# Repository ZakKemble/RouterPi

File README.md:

# RouterPi

Another Raspberry Pi router!

https://blog.zakkemble.net/routerpi-compute-module-4-router/

--------

Zak Kemble

contact@zakkemble.net

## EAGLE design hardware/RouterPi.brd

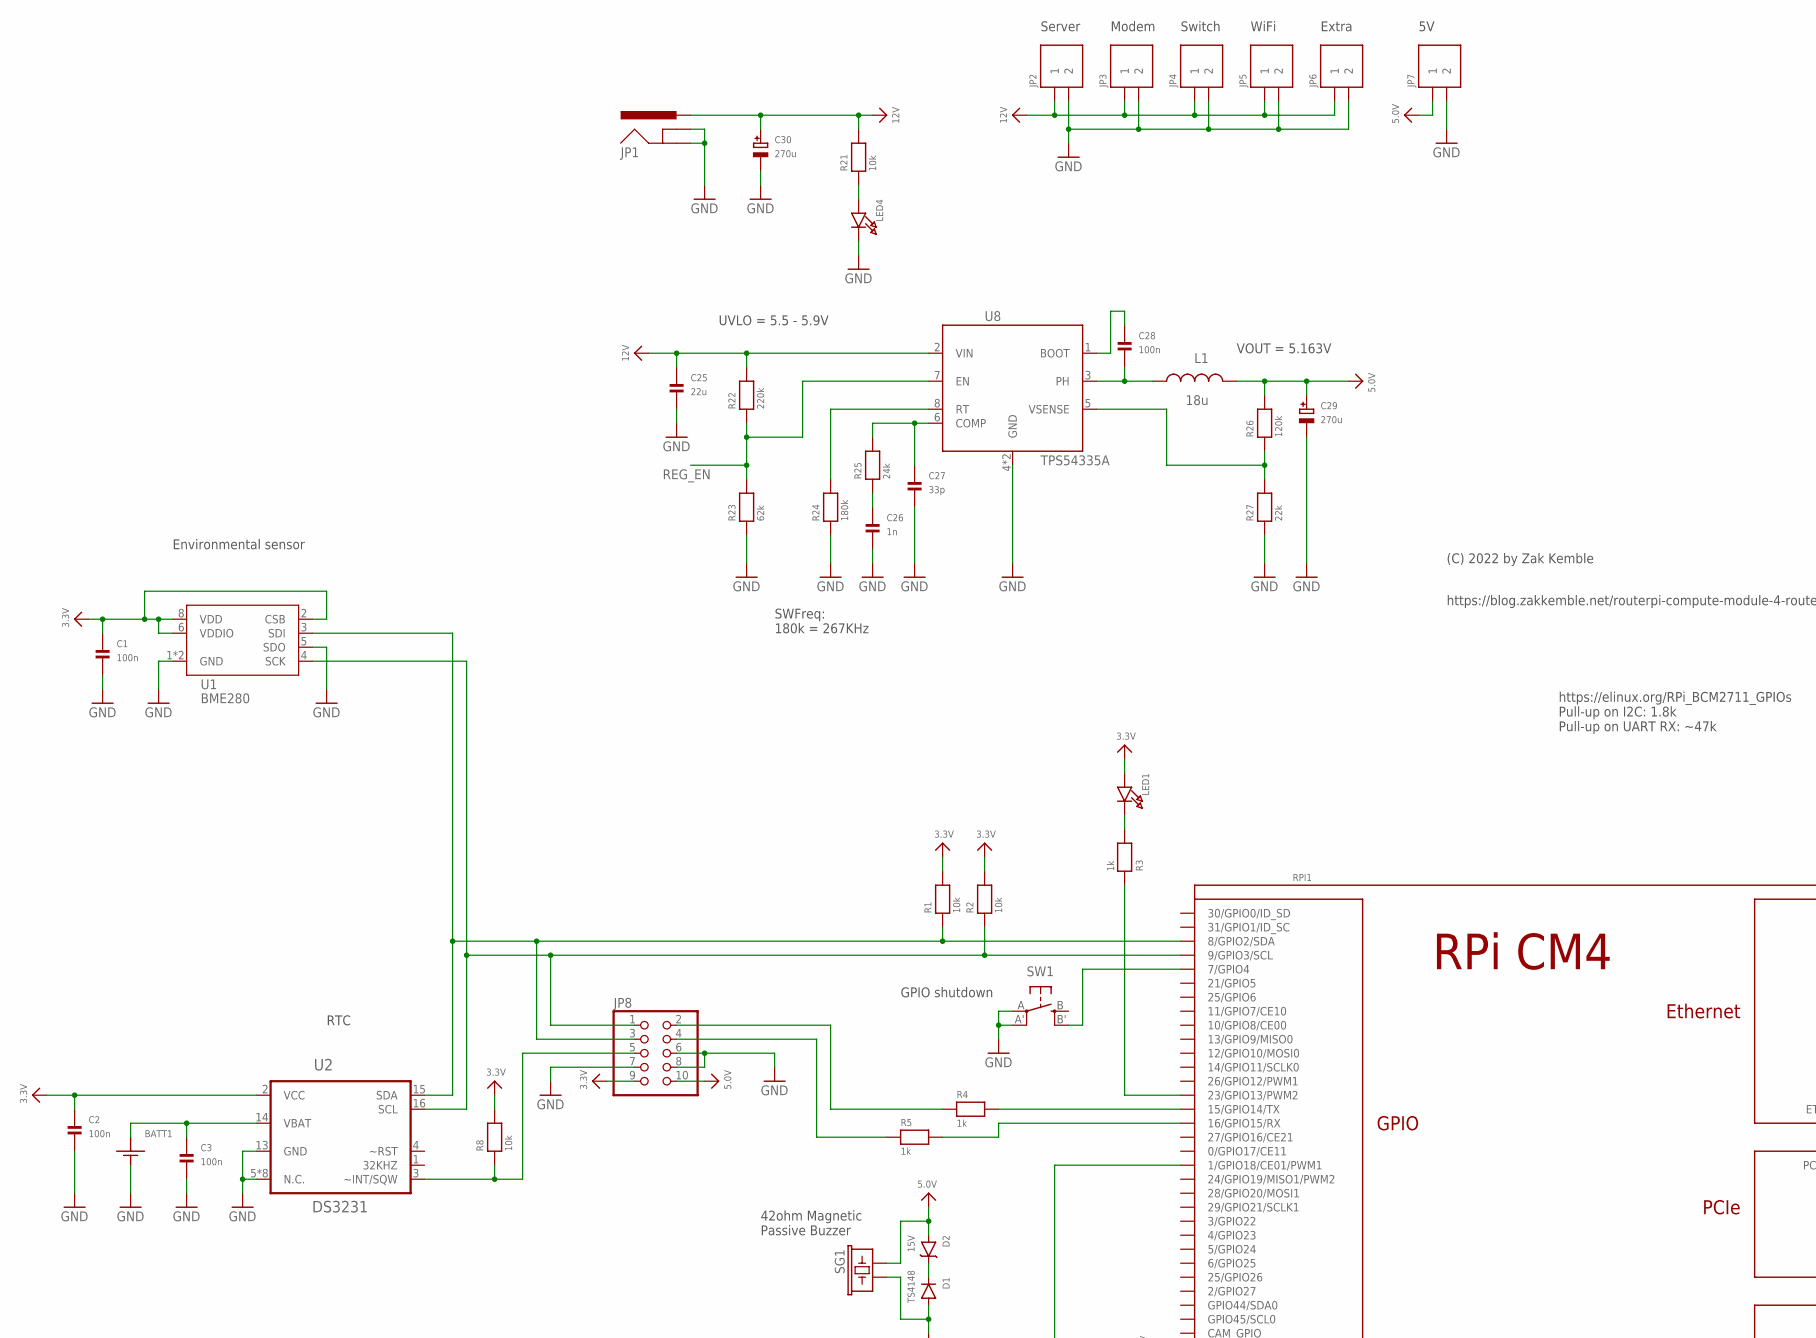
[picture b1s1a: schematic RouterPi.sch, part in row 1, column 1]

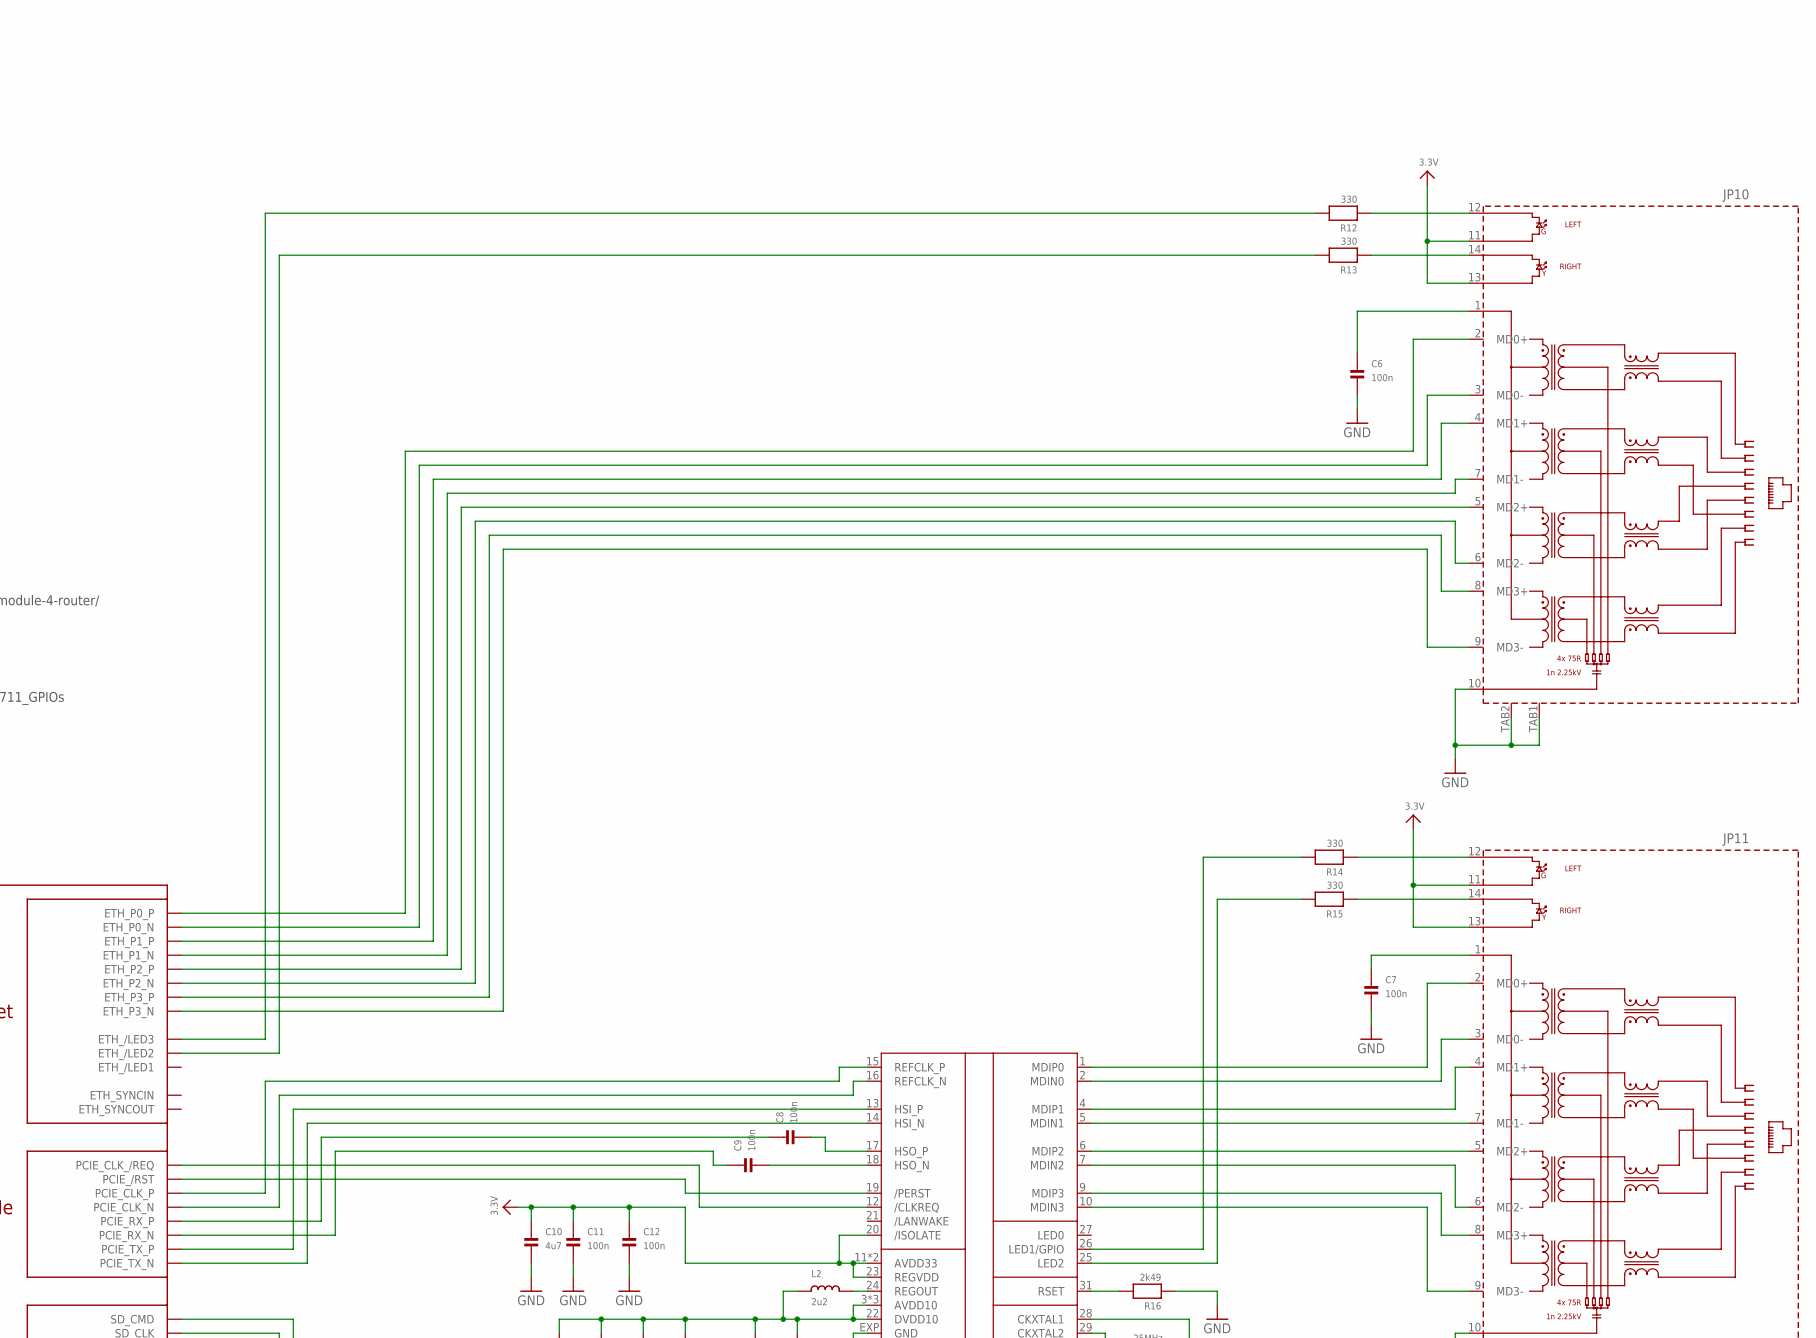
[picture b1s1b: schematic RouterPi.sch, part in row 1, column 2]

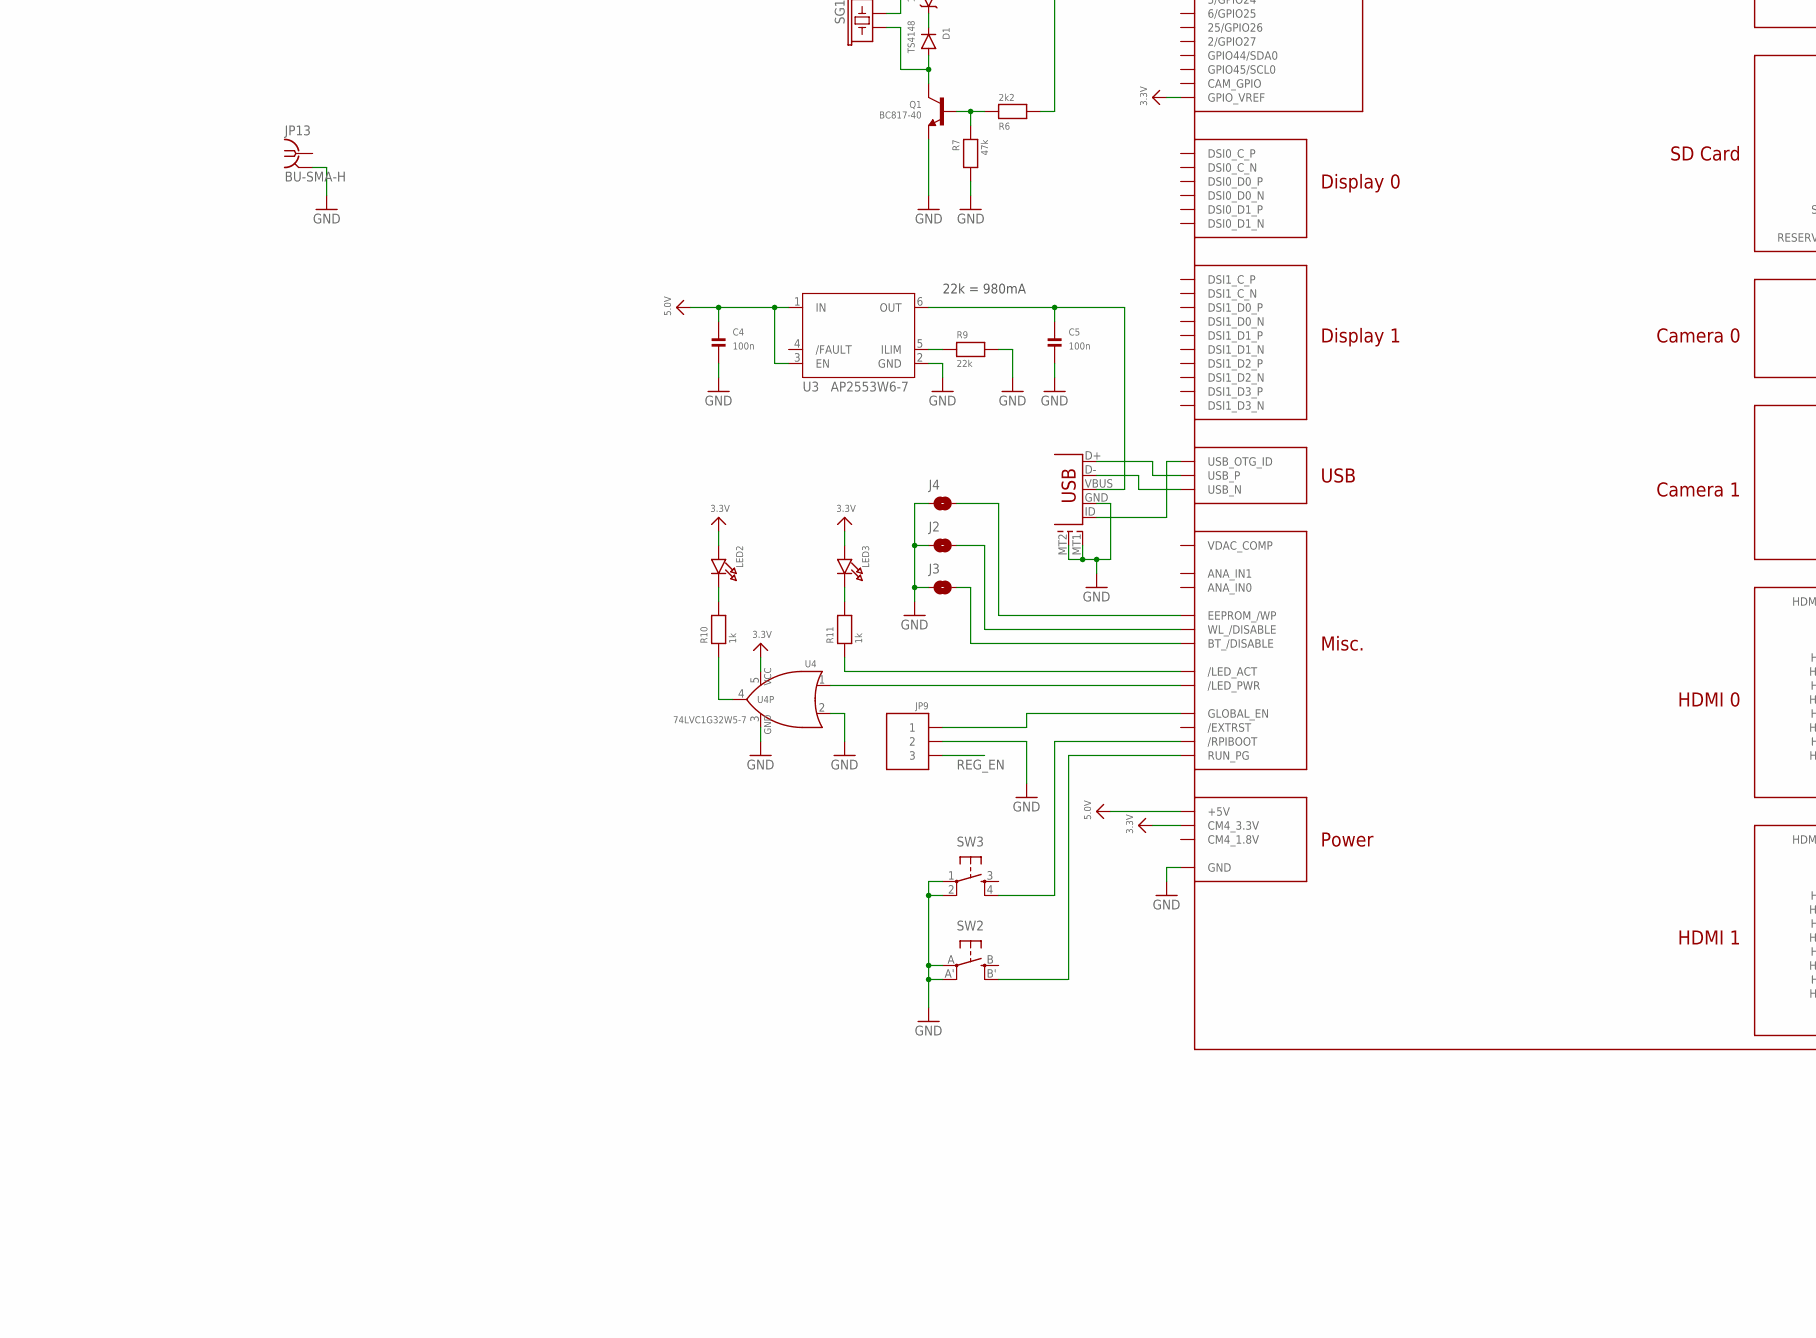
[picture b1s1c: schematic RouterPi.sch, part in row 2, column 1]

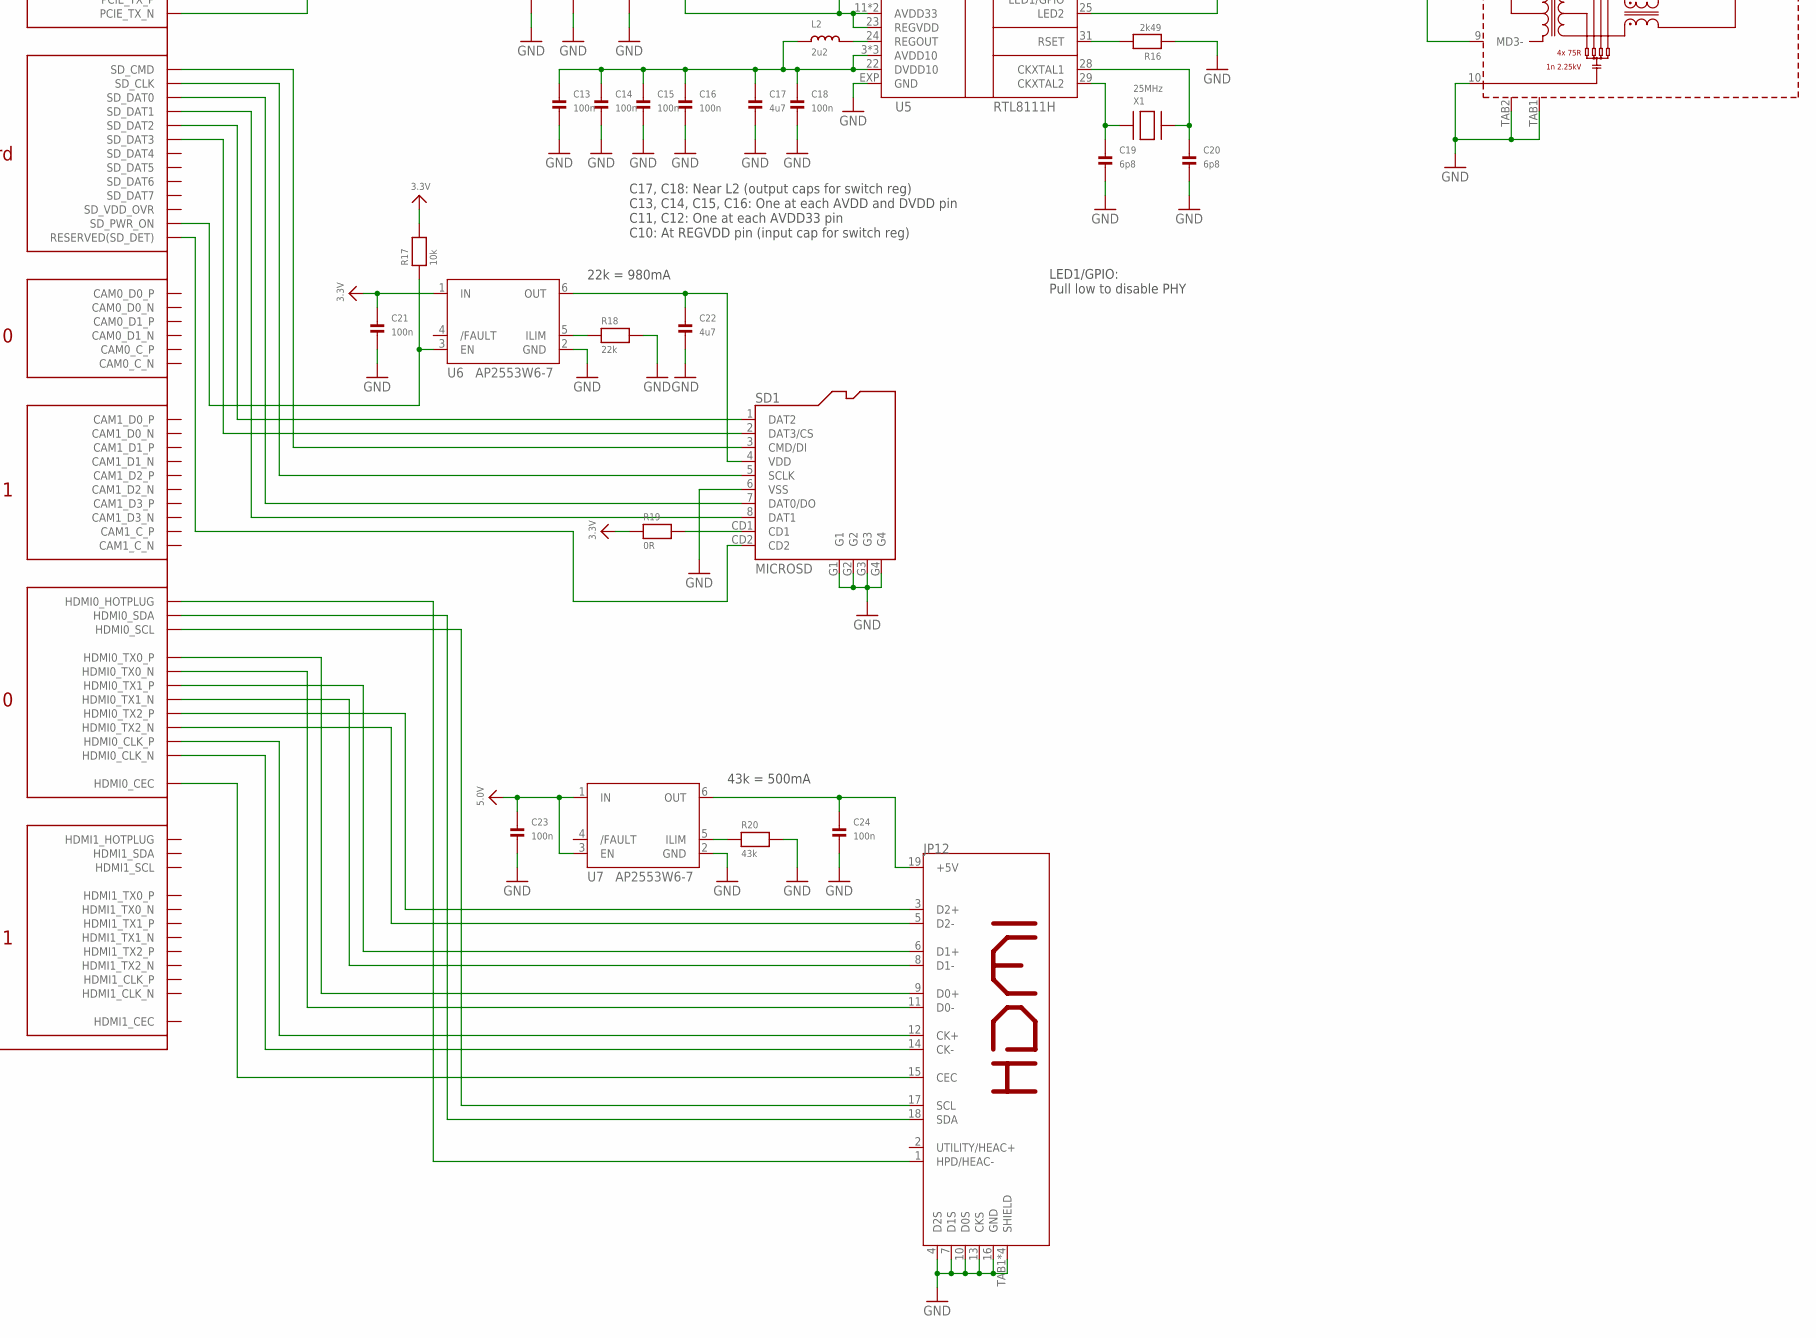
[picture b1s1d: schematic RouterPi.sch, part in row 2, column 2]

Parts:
BATT1: BATTERY_CR927
C1, C2, C3, C4, C5, C6, C7, C8, C9, C11, C12, C13, C14, C15, C16, C18, C21, C23, C24, C28: 100n; 0402_XSMALL
C10, C17: 4u7; _0603MP; FARNELL 2611924
C19, C20: 6p8; 0402_XSMALL
C22: 4u7; _0603MP
C25: 22u; 1210K; PARTNUM C3225X5R1C226M250AA; FARNELL 2526285
C26: 1n; 0402_XSMALL
C27: 33p; 0402_XSMALL
C29, C30: 270u; PANASONIC_D; PARTNUM 16SVPG270M; FARNELL 2491823
D1: TS4148; 0805_DIODE
D2: 15V; SOT-23-SLIMPAD; PARTNUM BZX84-C15
J2, J3, J4: JUMPERSMALL; JUMPER_SMALL
JP1: POWER_JACKPTH_HIGHCURRENT; POWER_JACK_PTH_HIGHCURRENT
JP2, JP3, JP4, JP5, JP6, JP7: 2WAY
JP8: PINHD-2X5; 2X05
JP9: HEADER_3WAY2.0MM; HEADER_2.0_3WAY
JP10, JP11: RJ45_MAG_MOLEX_93626
JP12: HDMIMICRO2; HDMI_MICRO2
JP13: BU-SMA-H
L1: 18u; CDRH125; PARTNUM SRR1210-180M; FARNELL 2408814
L2: 2u2; INDUCTOR_3X3MM_SM; FARNELL 2616857
LED1, LED2, LED3, LED4: LED0603_NOOUTLINE; CHIPLED_0603_NOOUTLINE
Q1: BC817-40; SOT23-R
R1, R2, R8, R17, R21: 10k; 0402_XSMALL
R3, R4, R5, R10, R11: 1k; 0402_XSMALL
R6: 2k2; 0402_XSMALL
R7: 47k; 0402_XSMALL
R9, R18, R27: 22k; 0402_XSMALL
R12, R13, R14, R15: 330; 0402_XSMALL
R16: 2k49; 0402_XSMALL
R19: 0R; 0402_XSMALL
R20: 43k; 0402_XSMALL
R22: 220k; 0402_XSMALL
R23: 62k; 0402_XSMALL
R24: 180k; 0402_XSMALL
R25: 24k; 0402_XSMALL
R26: 120k; 0402_XSMALL
RPI1: RPI_CM4RPI_CM4; RPI_CM4
SD1: MICROSD
SG1: BUZZERPTH; BUZZER-12MM
SW1, SW2: SPST_TACTMC32882; TACT_SMD4
SW3: SPST_TACTG75_3X4; TACT_SMD5
U1: BME280
U2: DS3231; SOIC127P1032X265-16N
U3, U6, U7: AP2553W6-7; SOT23-6_SM_PAD
U4: 74LVC1G32W5-7; SOT23-5_SM_PAD
U5: RTL8111H; QFN32-4X4-0.4
U8: TPS54335A; SOIC8_150MIL_EXPPAD
USB1: USB-MICROBLARGEPAD; USB-MICROB_LARGEPAD
X1: 25MHz; 2016_XTAL; PARTNO MCSJK-7F-25.00-10-20-60-B-20; FARNELL 2853847

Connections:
3.3V: C1.1, C2.1, C10.1, C11.1, C12.1, C21.1, JP8.9, JP10.11 (LED_L_A), JP10.13 (LED_R_A), JP11.11 (LED_L_A), JP11.13 (LED_R_A), LED1.A, LED2.A, LED3.A, R1.2, R2.2, R8.2, R17.2, R19.1, RPI1.78 (GPIO_VREF), RPI1.84 (CM4_3.3V), RPI1.86 (CM4_3.3V), U1.2 (CSB), U1.6 (VDDIO), U1.8 (VDD), U2.2 (VCC), U4.5 (VCC), U5.11 (AVDD33), U5.20 (/ISOLATE), U5.23 (REGVDD), U5.32 (AVDD33), U6.1 (IN)
5.0V: C4.1, C23.1, C29.+, D2.2 (A), JP7.P$1 (1), JP8.10, L1.2, R26.2, RPI1.77 (+5V), RPI1.79 (+5V), RPI1.81 (+5V), RPI1.83 (+5V), RPI1.85 (+5V), RPI1.87 (+5V), SG1.+ (1), U3.1 (IN), U3.3 (EN), U7.1 (IN), U7.3 (EN)
12V: C25.1, C30.+, JP1.PWR, JP2.P$1 (1), JP3.P$1 (1), JP4.P$1 (1), JP5.P$1 (1), JP6.P$1 (1), R21.2, R22.2, U8.2 (VIN)
GND: BATT1.B- (NEG), C1.2, C2.2, C3.2, C4.2, C5.2, C6.2, C7.2, C10.2, C11.2, C12.2, C13.2, C14.2, C15.2, C16.2, C17.2, C18.2, C19.2, C20.2, C21.2, C22.2, C23.2, C24.2, C25.2, C26.2, C27.2, C29.-, C30.-, J2.1, J3.1, J4.1, JP1.C1 (GNDBREAK), JP1.C2 (GNDBREAK), JP1.C3 (GNDBREAK), JP1.C4 (GNDBREAK), JP1.GND, JP2.P$2 (2), JP3.P$2 (2), JP4.P$2 (2), JP5.P$2 (2), JP6.P$2 (2), JP7.P$2 (2), JP8.6, JP8.7, JP8.8, JP9.2, JP10.10 (GND), JP10.TAB1, JP10.TAB2, JP11.10 (GND), JP11.TAB1, JP11.TAB2, JP12.4 (D2S), JP12.7 (D1S), JP12.10 (D0S), JP12.13 (CKS), JP12.16 (GND), JP12.TAB1 (SHIELD), JP12.TAB2 (SHIELD), JP12.TAB3 (SHIELD), JP12.TAB4 (SHIELD), JP13.2, JP13.3 (2), JP13.4 (2), JP13.5 (2), LED4.C, Q1.2 (E), R7.2, R9.2, R16.1, R18.2, R20.2, R23.1, R24.1, R27.1, RPI1.1 (GND), RPI1.2 (GND), RPI1.7 (GND), RPI1.8 (GND), RPI1.13 (GND), RPI1.14 (GND), RPI1.22 (GND), RPI1.23 (GND), RPI1.32 (GND), RPI1.33 (GND), RPI1.42 (GND), RPI1.43 (GND), RPI1.52 (GND), RPI1.53 (GND), RPI1.59 (GND), RPI1.60 (GND), RPI1.65 (GND), RPI1.66 (GND), RPI1.71 (GND), RPI1.74 (GND), RPI1.98 (GND), RPI1.107 (GND), RPI1.108 (GND), RPI1.113 (GND), RPI1.114 (GND), RPI1.119 (GND), RPI1.120 (GND), RPI1.125 (GND), RPI1.126 (GND), RPI1.131 (GND), RPI1.132 (GND), RPI1.137 (GND), RPI1.138 (GND), RPI1.144 (GND), RPI1.150 (GND), RPI1.155 (GND), RPI1.156 (GND), RPI1.161 (GND), RPI1.162 (GND), RPI1.167 (GND), RPI1.168 (GND), RPI1.173 (GND), RPI1.174 (GND), RPI1.179 (GND), RPI1.180 (GND), RPI1.185 (GND), RPI1.186 (GND), RPI1.191 (GND), RPI1.192 (GND), RPI1.197 (GND), RPI1.198 (GND), SD1.6 (VSS), SD1.G1, SD1.G2, SD1.G3, SD1.G4, SW1.A, SW1.A' (P1), SW2.A, SW2.A' (P1), SW3.1, SW3.2 (P1), U1.1 (GND), U1.5 (SDO), U1.7 (GND), U2.5 (N.C.), U2.6 (N.C.), U2.7 (N.C.), U2.8 (N.C.), U2.9 (N.C.), U2.10 (N.C.), U2.11 (N.C.), U2.12 (N.C.), U2.13 (GND), U3.2 (GND), U4.2 (B), U4.3 (GND), U5.EXP (GND), U6.2 (GND), U7.2 (GND), U8.4 (GND), U8.EXPPAD (GND), USB1.GND, USB1.MT1 (SHEILD1), USB1.MT2 (SHEILD2)
unnamed: C28.1, U8.1 (BOOT)
unnamed: R10.1, U4.4 (Y)
unnamed: R24.2, U8.8 (RT)
unnamed: C27.1, R25.2, U8.6 (COMP)
unnamed: C26.1, R25.1
unnamed: JP8.5, R8.1, U2.3 (~INT/SQW)
unnamed: JP12.9 (D0+), RPI1.182 (HDMI0_TX0_P)
unnamed: JP8.3, R1.1, RPI1.58 (8/GPIO2/SDA), U1.3 (SDI), U2.15 (SDA)
unnamed: JP12.11 (D0-), RPI1.184 (HDMI0_TX0_N)
unnamed: JP12.6 (D1+), RPI1.176 (HDMI0_TX1_P)
unnamed: JP12.8 (D1-), RPI1.178 (HDMI0_TX1_N)
unnamed: D1.1 (A), Q1.3 (C), SG1.- (2)
unnamed: C28.2, L1.1, U8.3 (PH)
unnamed: R26.1, R27.2, U8.5 (VSENSE)
unnamed: Q1.1 (B), R6.1, R7.1
unnamed: JP12.3 (D2+), RPI1.170 (HDMI0_TX2_P)
unnamed: J3.2, RPI1.91 (BT_/DISABLE)
unnamed: J2.2, RPI1.89 (WL_/DISABLE)
unnamed: BATT1.B+ (POS), C3.1, U2.14 (VBAT)
unnamed: JP12.5 (D2-), RPI1.172 (HDMI0_TX2_N)
unnamed: JP8.2, R4.1
unnamed: JP12.12 (CK+), RPI1.188 (HDMI0_CLK_P)
unnamed: JP8.1, R2.1, RPI1.56 (9/GPIO3/SCL), U1.4 (SCK), U2.16 (SCL)
unnamed: JP12.14 (CK-), RPI1.190 (HDMI0_CLK_N)
unnamed: R11.1, RPI1.21 (/LED_ACT)
unnamed: RPI1.95 (/LED_PWR), U4.1 (A)
unnamed: JP9.1, RPI1.99 (GLOBAL_EN)
unnamed: RPI1.93 (/RPIBOOT), SW3.4 (S1)
unnamed: LED4.A, R21.1
unnamed: D1.2 (C), D2.1 (C)
unnamed: RPI1.92 (RUN_PG), SW2.B' (S1)
unnamed: L2.P$2 (2), U5.24 (REGOUT)
unnamed: R16.2, U5.31 (RSET)
unnamed: C19.1, U5.29 (CKXTAL2), X1.1
unnamed: C20.1, U5.28 (CKXTAL1), X1.3
unnamed: JP11.2 (MD0+), U5.1 (MDIP0)
unnamed: R15.2, U5.25 (LED2)
unnamed: R14.2, U5.26 (LED1/GPIO)
unnamed: JP11.3 (MD0-), U5.2 (MDIN0)
unnamed: JP11.4 (MD1+), U5.4 (MDIP1)
unnamed: JP11.7 (MD1-), U5.5 (MDIN1)
unnamed: JP11.5 (MD2+), U5.6 (MDIP2)
unnamed: JP11.6 (MD2-), U5.7 (MDIN2)
unnamed: JP11.8 (MD3+), U5.9 (MDIP3)
unnamed: JP11.9 (MD3-), U5.10 (MDIN3)
unnamed: JP8.4, R5.1
unnamed: RPI1.61 (SD_DAT3), SD1.2 (DAT3/CS)
unnamed: C9.2, U5.18 (HSO_N)
unnamed: C8.1, RPI1.116 (PCIE_RX_P)
unnamed: RPI1.62 (SD_CMD), SD1.3 (CMD/DI)
unnamed: RPI1.63 (SD_DAT0), SD1.7 (DAT0/DO)
unnamed: C13.1, C14.1, C15.1, C16.1, C17.1, C18.1, L2.P$1 (1), U5.3 (AVDD10), U5.8 (AVDD10), U5.22 (DVDD10), U5.30 (AVDD10)
unnamed: JP10.12 (LED_L_C), R12.1
unnamed: C7.1, JP11.1 (VCC)
unnamed: C6.1, JP10.1 (VCC)
unnamed: J4.2, RPI1.20 (EEPROM_/WP)
unnamed: JP10.14 (LED_R_C), R13.1
unnamed: C5.1, U3.6 (OUT), USB1.VBUS
unnamed: RPI1.76 (RESERVED(SD_DET)), SD1.CD2
unnamed: JP12.15 (CEC), RPI1.151 (HDMI0_CEC)
unnamed: JP12.17 (SCL), RPI1.200 (HDMI0_SCL)
unnamed: JP12.18 (SDA), RPI1.199 (HDMI0_SDA)
unnamed: JP12.1 (HPD/HEAC-), RPI1.153 (HDMI0_HOTPLUG)
unnamed: R17.1, RPI1.75 (SD_PWR_ON), U6.3 (EN)
unnamed: RPI1.102 (PCIE_CLK_/REQ), U5.12 (/CLKREQ)
unnamed: RPI1.103 (USB_N), USB1.D-
unnamed: RPI1.105 (USB_P), USB1.D+
unnamed: RPI1.101 (USB_OTG_ID), USB1.ID
unnamed: RPI1.109 (PCIE_/RST), U5.19 (/PERST)
unnamed: RPI1.110 (PCIE_CLK_P), U5.15 (REFCLK_P)
unnamed: RPI1.112 (PCIE_CLK_N), U5.16 (REFCLK_N)
unnamed: C8.2, U5.17 (HSO_P)
unnamed: C9.1, RPI1.118 (PCIE_RX_N)
unnamed: RPI1.122 (PCIE_TX_P), U5.13 (HSI_P)
unnamed: RPI1.124 (PCIE_TX_N), U5.14 (HSI_N)
unnamed: JP10.2 (MD0+), RPI1.12 (ETH_P0_P)
unnamed: JP10.3 (MD0-), RPI1.10 (ETH_P0_N)
unnamed: JP10.4 (MD1+), RPI1.4 (ETH_P1_P)
unnamed: JP10.7 (MD1-), RPI1.6 (ETH_P1_N)
unnamed: JP10.5 (MD2+), RPI1.11 (ETH_P2_P)
unnamed: JP10.6 (MD2-), RPI1.9 (ETH_P2_N)
unnamed: JP10.8 (MD3+), RPI1.3 (ETH_P3_P)
unnamed: JP10.9 (MD3-), RPI1.5 (ETH_P3_N)
unnamed: C24.1, JP12.19 (+5V), U7.6 (OUT)
unnamed: C22.1, SD1.4 (VDD), U6.6 (OUT)
unnamed: R6.2, RPI1.49 (1/GPIO18/CE01/PWM1)
unnamed: RPI1.54 (7/GPIO4), SW1.B' (S1)
unnamed: JP11.12 (LED_L_C), R14.1
unnamed: JP11.14 (LED_R_C), R15.1
unnamed: R4.2, RPI1.55 (15/GPIO14/TX)
unnamed: R5.2, RPI1.51 (16/GPIO15/RX)
unnamed: R12.2, RPI1.15 (ETH_/LED3)
unnamed: R13.2, RPI1.17 (ETH_/LED2)
unnamed: RPI1.67 (SD_DAT1), SD1.8 (DAT1)
unnamed: RPI1.57 (SD_CLK), SD1.5 (SCLK)
unnamed: RPI1.69 (SD_DAT2), SD1.1 (DAT2)
unnamed: R3.1, RPI1.28 (23/GPIO13/PWM2)
unnamed: R9.1, U3.5 (ILIM)
unnamed: R20.1, U7.5 (ILIM)
unnamed: LED1.C, R3.2
unnamed: LED3.C, R11.2
unnamed: R18.1, U6.5 (ILIM)
unnamed: R19.2, SD1.CD1
unnamed: LED2.C, R10.2
REG_EN: JP9.3, R22.1, R23.2, U8.7 (EN)

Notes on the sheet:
(C) 2022 by Zak Kemble
GPIO shutdown
https://elinux.org/RPi_BCM2711_GPIOs Pull-up on I2C: 1.8k Pull-up on UART RX: ~47k
C17, C18: Near L2 (output caps for switch reg) C13, C14, C15, C16: One at each AVDD and DVDD pin C11, C12: One at each AVDD33 pin C10: At REGVDD pin (input cap for switch reg)
22k = 980mA
43k = 500mA
UVLO = 5.5 - 5.9V
SWFreq: 180k = 267KHz
Server
Modem
Switch
WiFi
Extra
42ohm Magnetic Passive Buzzer
VOUT = 5.163V
LED1/GPIO: Pull low to disable PHY
RTC
Environmental sensor
https://blog.zakkemble.net/routerpi-compute-module-4-router/

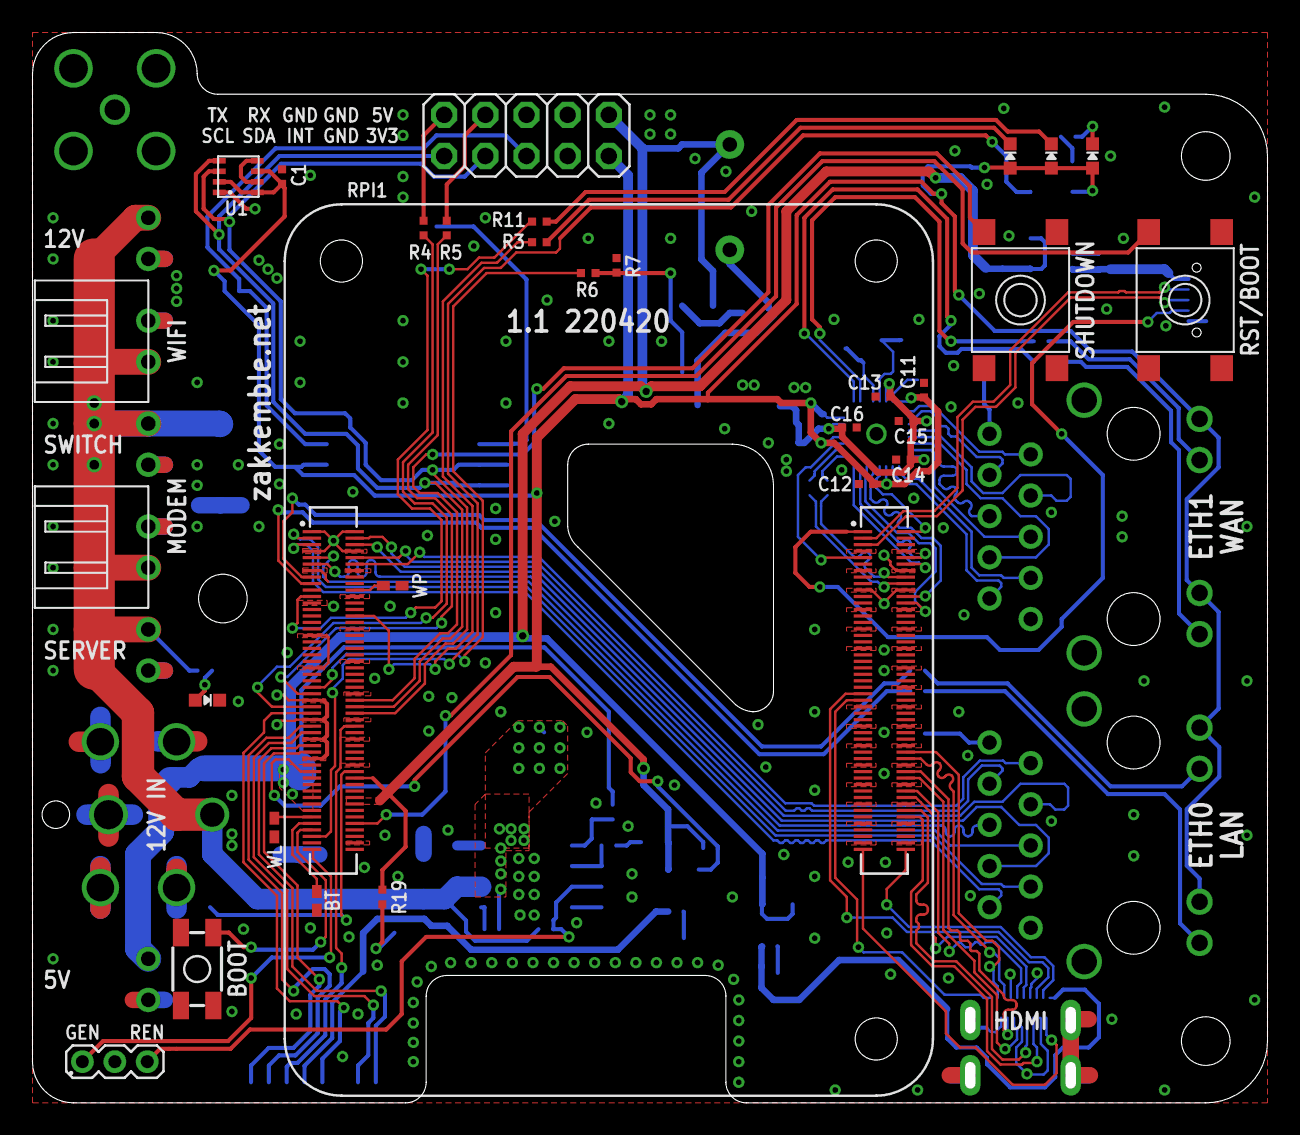
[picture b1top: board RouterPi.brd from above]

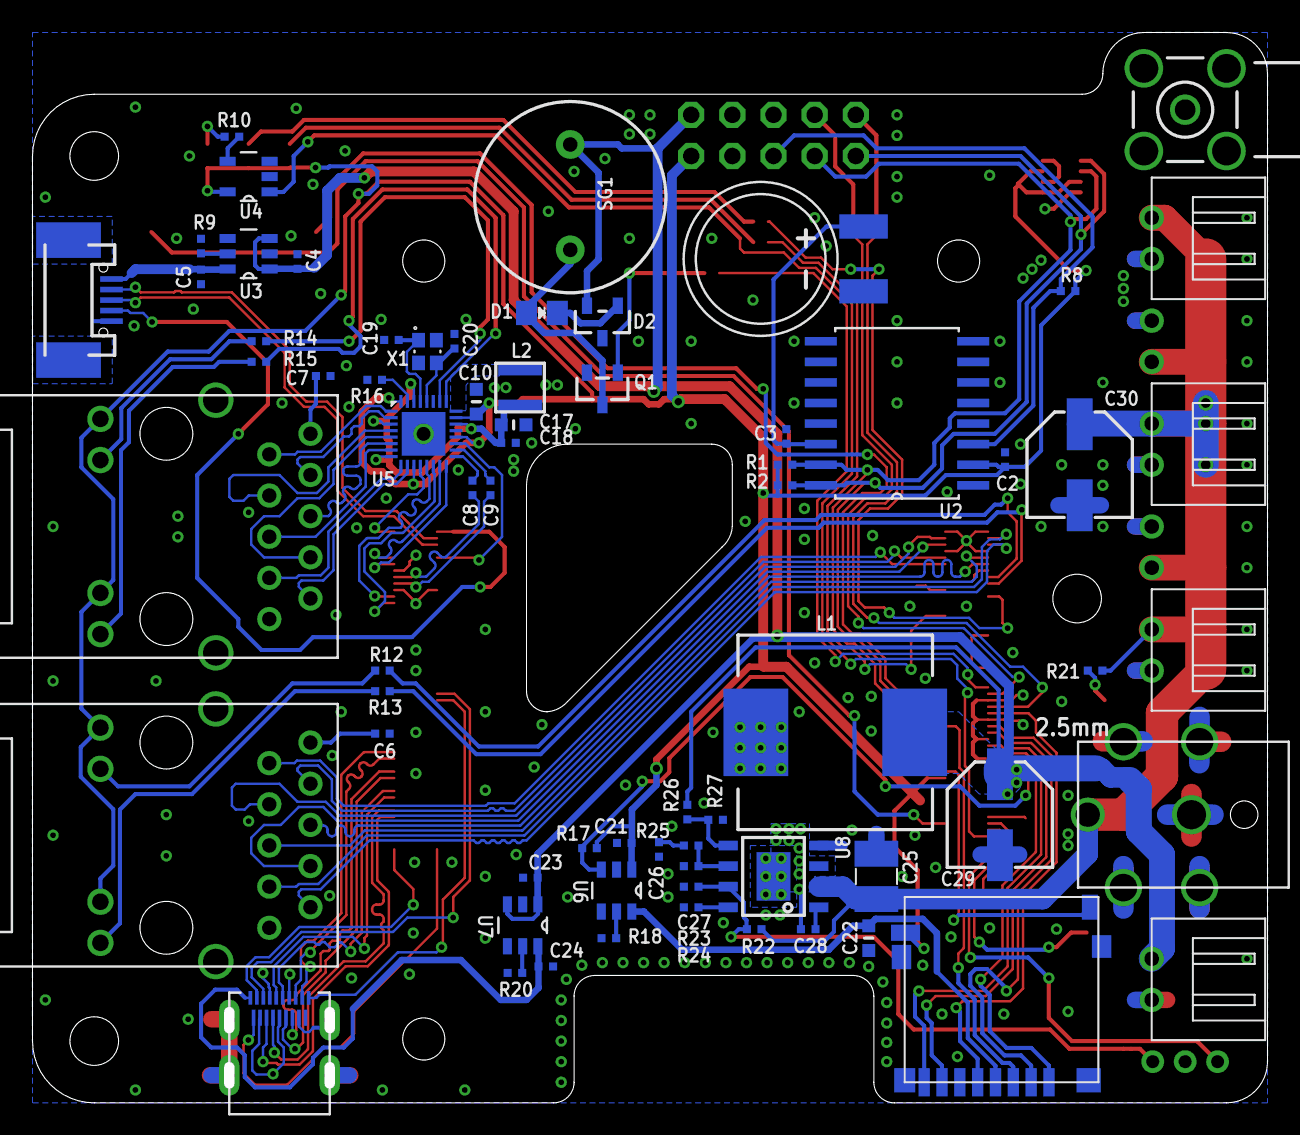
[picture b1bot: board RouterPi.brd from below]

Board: 2 copper layers, 76.2 x 66.0 mm, 99 parts (69 on the bottom side), 109 nets.

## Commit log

2022-04-19 Add readme
2022-04-19 Add schematic and PCB designs
2022-04-19 Another readme for software configs
2022-04-19 sysctl.conf: add default config
2022-04-19 config.txt: add default config
2022-04-19 named: add default config
2022-04-19 ifplugd: add default config
2022-04-19 dhcpcd: add default config
2022-04-19 rc.local: add default
2022-04-19 named: configure recursive DNS resolver
2022-04-19 ifplugd: configure
2022-04-20 dhcpcd: configure
2022-04-20 rc.local: run script on boot
2022-04-20 sysctl.conf: enable IP forwarding
2022-04-20 sshd: enable keepalive
2022-04-20 ppp: add default config
2022-04-20 ppp: configure
2022-04-20 dnsmasq: configure DHCP
2022-04-20 script: show DHCP leases
2022-04-20 script: show temperatures
2022-04-20 script: configure firewall/NAT
2022-04-20 script: do stuff at boot
2022-04-20 script: beep tunes
2022-04-20 config.txt: configure
2022-04-20 Fix image link
2022-08-17 readme: disable man-db
2022-08-17 script: enable interrupt coalescing

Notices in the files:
parts and their libraries:
microbuilder: This work is placed in the public domain, and may be freely used for commercial and non-commercial work with the following conditions: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
SparkFun-Electromechanical: Licensing: CC v3.0 Share-Alike You are welcome to use this library for commercial purposes.
